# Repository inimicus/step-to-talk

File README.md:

# Step-to-Talk

Simple VUSB-based programmable keyboard.

Based on work by [Daniel Thompson](mailto:daniel@redfelineninja.org.uk) on 
[RFStompbox](http://www.redfelineninja.org.uk/software/rfstompbox.html) 
incorporating Objective Development's firmware-only USB driver for Atmel's AVR 
microcontrollers, [VUSB](http://www.obdev.at/products/vusb/).

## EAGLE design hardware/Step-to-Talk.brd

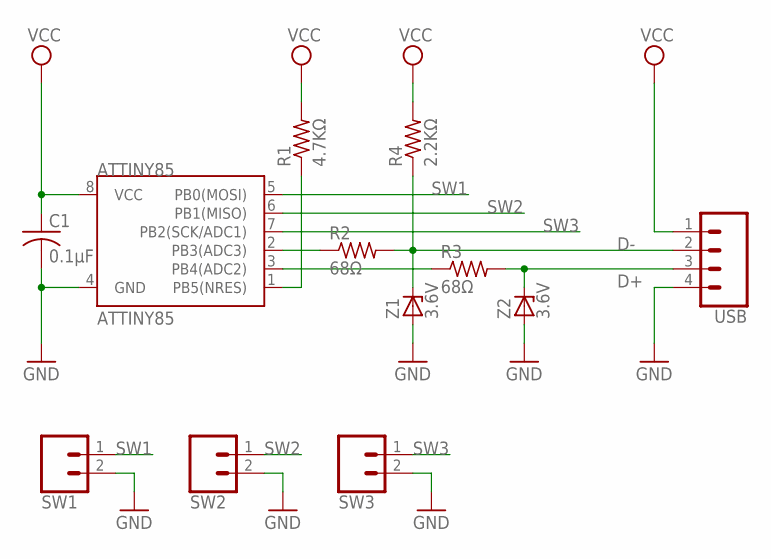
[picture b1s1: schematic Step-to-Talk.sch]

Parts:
ATTINY85: ATTINY85; DIP08_MCU
C1: 0.1µF; C025-024X044
R1: 4.7KΩ; 0204/5
R2, R3: 68Ω; 0204/5
R4: 2.2KΩ; 0204/5
SW1, SW2, SW3: CONN_02; 1X02
USB: CONN_04LONGPADS; 1X04_LONGPADS
Z1, Z2: 3.6V; ZDIO-5

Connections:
D+: R3.2, USB.3, Z2.C
D-: R2.2, R4.1, USB.2, Z1.C
GND: ATTINY85.4 (GND), C1.2, SW1.2, SW2.2, SW3.2, USB.4, Z1.A, Z2.A
unnamed: ATTINY85.1 (PB5(NRES)), R1.1
unnamed: ATTINY85.3 (PB4(ADC2)), R3.1
unnamed: ATTINY85.2 (PB3(ADC3)), R2.1
SW1: ATTINY85.5 (PB0(MOSI)), SW1.1
SW2: ATTINY85.6 (PB1(MISO)), SW2.1
SW3: ATTINY85.7 (PB2(SCK/ADC1)), SW3.1
VCC: ATTINY85.8 (VCC), C1.1, R1.2, R4.2, USB.1

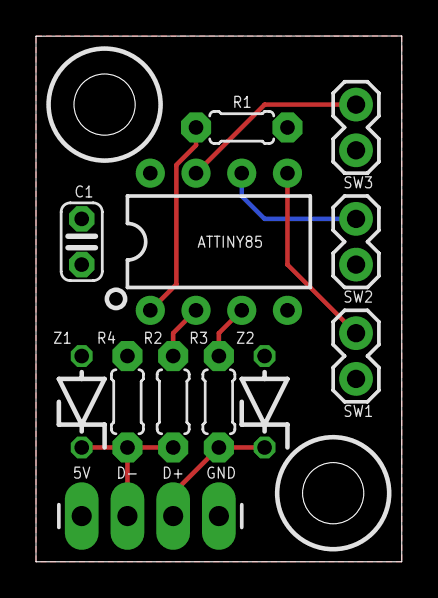
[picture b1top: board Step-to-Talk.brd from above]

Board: 2 copper layers, 20.3 x 29.2 mm, 12 parts (0 on the bottom side), 10 nets.

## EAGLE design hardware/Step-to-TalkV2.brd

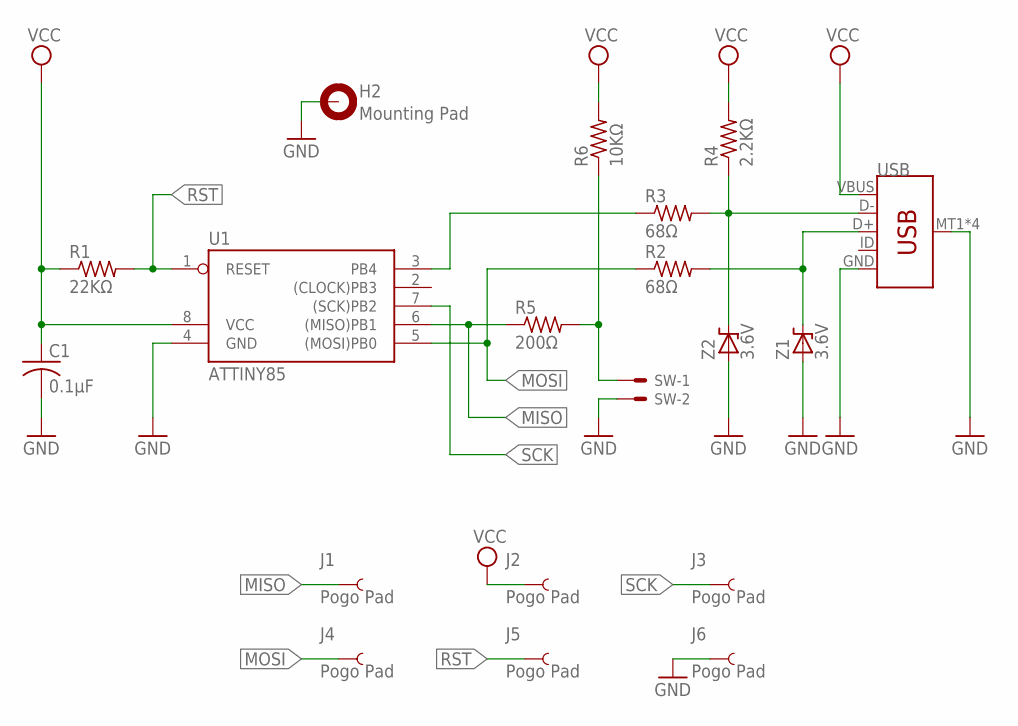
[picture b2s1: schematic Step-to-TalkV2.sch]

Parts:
C1: 0.1µF; C0603
H2: Mounting Pad; 4,3-PAD
J1, J2, J3, J4, J5, J6: Pogo Pad; PAD.03X.03
R1: 22KΩ; R0603
R2, R3: 68Ω; R0603
R4: 2.2KΩ; R0603
R5: 200Ω; R0603
R6: 10KΩ; R0603
SW: 87438-02
U1: ATTINY85; SOIC8
USB: USB_MICRO-B_SMT; USB-MICROB
Z1, Z2: 3.6V; SOD523-ENLARGED

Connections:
D+: R2.2, USB.D+, Z1.1 (K)
D-: R3.2, R4.1, USB.D-, Z2.1 (K)
GND: C1.2, H2.B4,3, J6.P$1, SW.2, U1.4 (GND), USB.GND, USB.MT1 (SHIELD), USB.MT2 (SHIELD), USB.P$1 (SHIELD), USB.P$2 (SHIELD), Z1.2 (A), Z2.2 (A)
MISO: J1.P$1, R5.1, U1.6 ((MISO)PB1)
MOSI: J4.P$1, R2.1, U1.5 ((MOSI)PB0)
unnamed: R3.1, U1.3 (PB4)
unnamed: R5.2, R6.1, SW.1
RST: J5.P$1, R1.2, U1.1 (RESET)
SCK: J3.P$1, U1.7 ((SCK)PB2)
VCC: C1.1, J2.P$1, R1.1, R4.2, R6.2, U1.8 (VCC), USB.VBUS

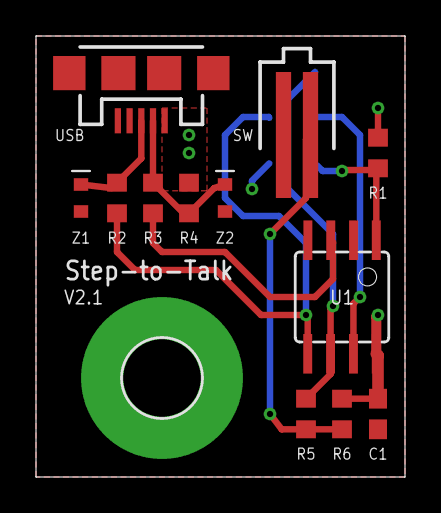
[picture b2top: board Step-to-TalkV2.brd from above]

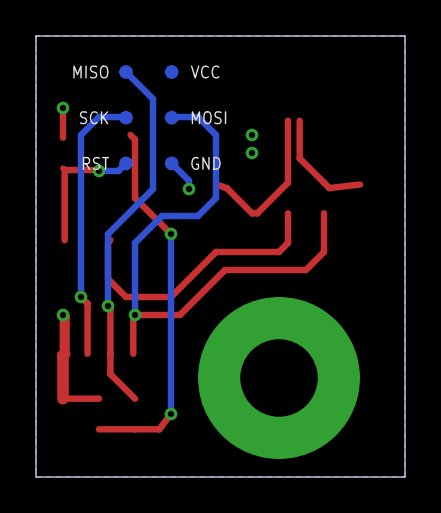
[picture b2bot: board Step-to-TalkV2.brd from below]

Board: 2 copper layers, 20.5 x 24.5 mm, 19 parts (6 on the bottom side), 10 nets.

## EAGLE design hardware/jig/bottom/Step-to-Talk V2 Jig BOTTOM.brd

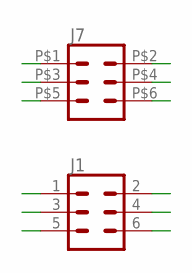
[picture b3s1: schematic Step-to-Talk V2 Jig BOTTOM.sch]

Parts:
J1: CONN_03X2NO_SILK; 2X3-NS
J7: CONN_03X2POGO_PINS; 2X3_POGO

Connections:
GND: J1.6, J7.P$5 (5)
MISO: J1.1, J7.P$2 (2)
MOSI: J1.4, J7.P$3 (3)
RST: J1.5, J7.P$6 (6)
SCK: J1.3, J7.P$4 (4)
VCC: J1.2, J7.P$1 (1)

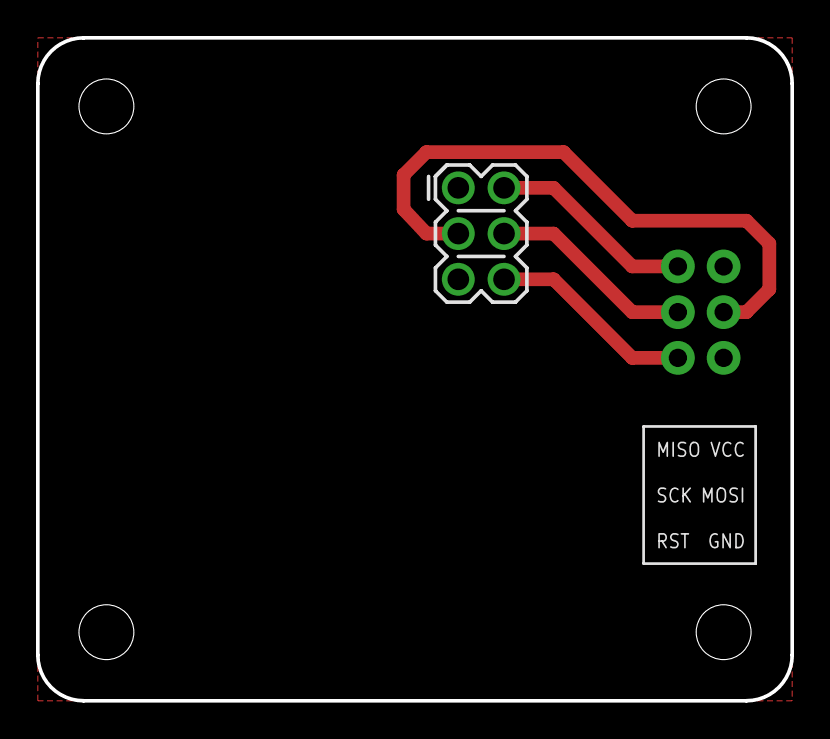
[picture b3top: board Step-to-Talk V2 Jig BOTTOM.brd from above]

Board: 2 copper layers, 41.9 x 36.8 mm, 6 parts (0 on the bottom side), 6 nets.

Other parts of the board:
U$1, U$2, U$3, U$4: STAND-OFF-TIGHT

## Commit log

2017-05-10 Initial commit.
2017-05-10 Add readme.
2017-05-16 Remove trailing whitespace.
2017-05-18 Fix button logic. No longer functions opposite of intended.
2017-05-18 Remove rogue backtick.
2017-06-09 Update comment and whitespace style.
2017-06-09 Add YCM configuration.
2017-06-09 Add additional button support.
2017-06-13 Remove testPoll function.
2017-06-13 Cleanup comments.
2017-06-13 Addition YCM compile flags (ignore unknown attributes).
2017-06-14 Add initial support for modifier keys.
2017-06-14 Testing of modifiers and simultaneous key presses.
2017-06-15 Initial functionality of support for multiple key presses, including modifier keys.
2017-06-15 Slight cleanup, adjustments.
2017-06-16 Add command line utility with ability to program, save to EEPROM.
2017-06-19 Add YCM extra conf for command line tool.
2017-06-19 Remove unused command line options.
2017-06-19 Command line cleanup.
2017-06-19 Bump serial number.
2017-06-19 Comment style update.
2017-06-19 Add functional updating via commandline.
2017-06-19 Include common model name in descriptor.
2017-06-19 Remove leftover reference material.
2017-06-21 Cleaned up and rearranged command line utility.
    - Renamed libs (micronucleus -> steptotalk)
    - Added banner/formatting to CLI output
    - Moved functions to steptotalk_lib, cleaned up header
    - Added descriptions to functions
    - Added header commend to main file
    - Made the help more fancy
2017-06-21 Remove bottom banner from firmware file.
2017-06-21 Don't include avr/iotn85.h directly.
2017-06-21 Remove dSYM during make clean.
2017-06-22 Clear trailing whitespace.
2017-06-22 Inital work on macOS UI.
2017-06-22 Switch to and use libusb-1.0.
2017-06-22 Add condition to check for failures in sending updates.
2017-06-22 Additional checks for failure.
2017-06-26 Remove WIP app(s) from dev branch.
2017-07-07 Add USB close and free functions.
    Also improved whitespace for clarity and additional misc cleanup.
2017-09-01 Rework debouncing in poll, make debounce per-key rather than global.
2017-09-01 [WIP] Be more aware of the number of keys. Functionality still leaves much to be desired.
2017-09-01 Rework main loop to account for per-key debouncing.
2017-10-25 Add new board and schematic.
2017-10-25 Update port configuration.
2017-10-25 Modify for single-button operation only.
2017-10-25 Update name, remove serial number.
2017-10-26 Add release to modifier key.
2017-10-26 Update supported models list.
2017-10-26 Set modifier release to no modifier.
2017-10-26 With only one key, we don't need to OR the modifier press.
2017-10-26 Move send key up/down to their own basic functions.
2017-10-28 Use correct D+ pin in configuration.
2017-11-02 Consolidate keyboard actions.
2017-11-02 Key release changed to global 0, no longer need to define release state.
2017-11-02 Consolidate USB setup into its own function.
2017-11-02 Reduce debounce time to a sane amount.
2017-11-02 Elaborate on where hadUsbReset() is called from.
2017-11-15 Optimize routing, increase diode pad size.
2017-11-17 Move board files to their own directory.
2017-11-17 Add programming jig boards.
2017-11-17 Collect boards into their own folders.
2017-11-17 Update jig boards for printing.
2017-11-17 Add gerbmerge configuration file.
2017-11-17 Add gitignore and ignore generated gerber files.
2018-01-23 Update/increase middle layer drills to properly fit pogo pins.
2018-03-18 Update references avr-gcc version.
2018-03-18 Update VUSB.
2018-03-18 Add const keyword for descriptor.
2018-06-10 Add back multiple buttons support for STT03 model.
2020-09-26 Updated V2.1 board with removed thermals, vias on USB connector pads.
2026-02-15 Remove V2 board/jig from STT03 branch
2026-02-15 Add back STT03 board and schematic
2026-02-15 Update avrdude command
2026-02-15 Remove ycm config
2026-02-15 Use clang over gcc
2026-02-22 Update USBFLAGS and USBLIBS paths

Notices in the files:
parts and their libraries:
SparkFun-Connectors: Licensing: Creative Commons ShareAlike 4.0 International - https://creativecommons.org/licenses/by-sa/4.0
